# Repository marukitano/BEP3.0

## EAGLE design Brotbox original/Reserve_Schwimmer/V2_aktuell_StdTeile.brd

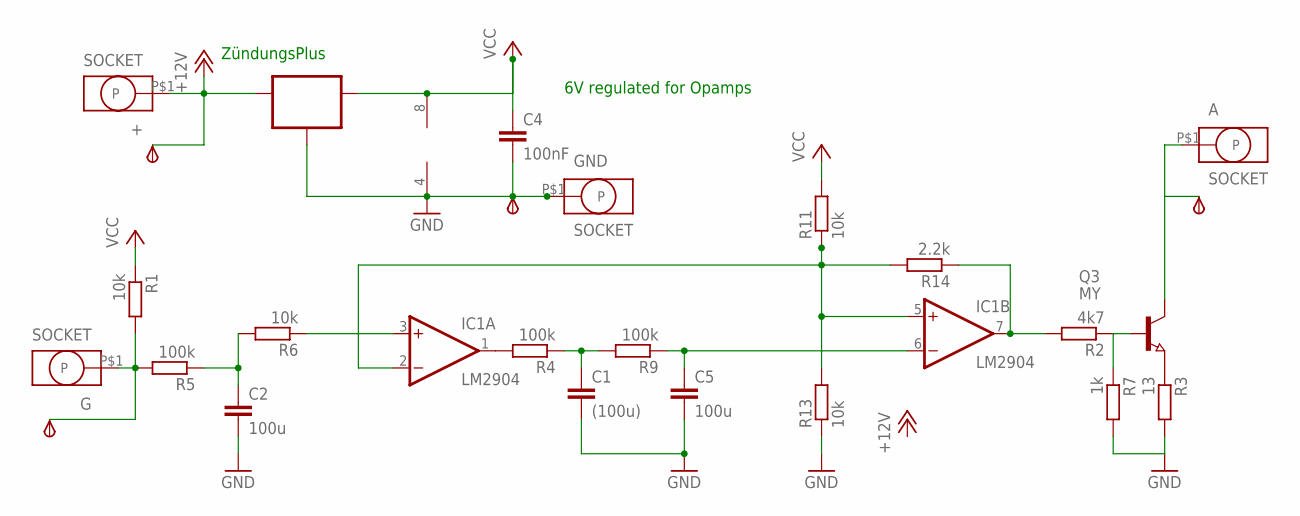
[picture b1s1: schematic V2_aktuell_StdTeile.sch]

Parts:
+: SOCKET; ID2.5MM
A: SOCKET; ID2.5MM
C1: (100u); C1206K
C2, C5: 100u; C1206K
C4: 100nF; C0805
G: SOCKET; ID2.5MM
GND: SOCKET; ID2.5MM
GND_: TPSB2.0; B2.0
IC1: LM2904; SO08
IC2: 70L06; SOT89_ROUND
IN: TPSB2.0; B2.0
OUT: TPSB2.0; B2.0
Q3: MY; SOT89
R1, R6, R11, R13: 10k; R0805
R2: 4k7; R0805
R3: 13; R1206
R4, R5, R9: 100k; R0805
R7: 1k; R0805
R14: 2.2k; R0805
V+: TPSB2.0; B2.0

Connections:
+12V: +.P$1, IC2.3 (IN), V+.TP
GND: C1.2, C2.2, C4.2, C5.2, GND.P$1, GND_.TP, IC1.4 (V-), IC2.2 (GND), IC2.2@1 (GND), R3.2, R7.2, R13.1
unnamed: C2.1, R5.1, R6.2
unnamed: Q3.1 (B), R2.1, R7.1
unnamed: C1.1, R4.1, R9.2
unnamed: C5.1, IC1.6 (-IN), R9.1
unnamed: IC1.2 (-IN), IC1.5 (+IN), R11.1, R13.2, R14.2
unnamed: G.P$1, IN.TP, R1.2, R5.2
unnamed: Q3.3 (E), R3.1
unnamed: IC1.3 (+IN), R6.1
unnamed: IC1.7 (OUT), R2.2, R14.1
unnamed: A.P$1, OUT.TP, Q3.2 (C)
unnamed: IC1.1 (OUT), R4.2
VCC: C4.1, IC1.8 (V+), IC2.1 (OUT), R1.1, R11.2

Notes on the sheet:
6V regulated for Opamps
ZündungsPlus

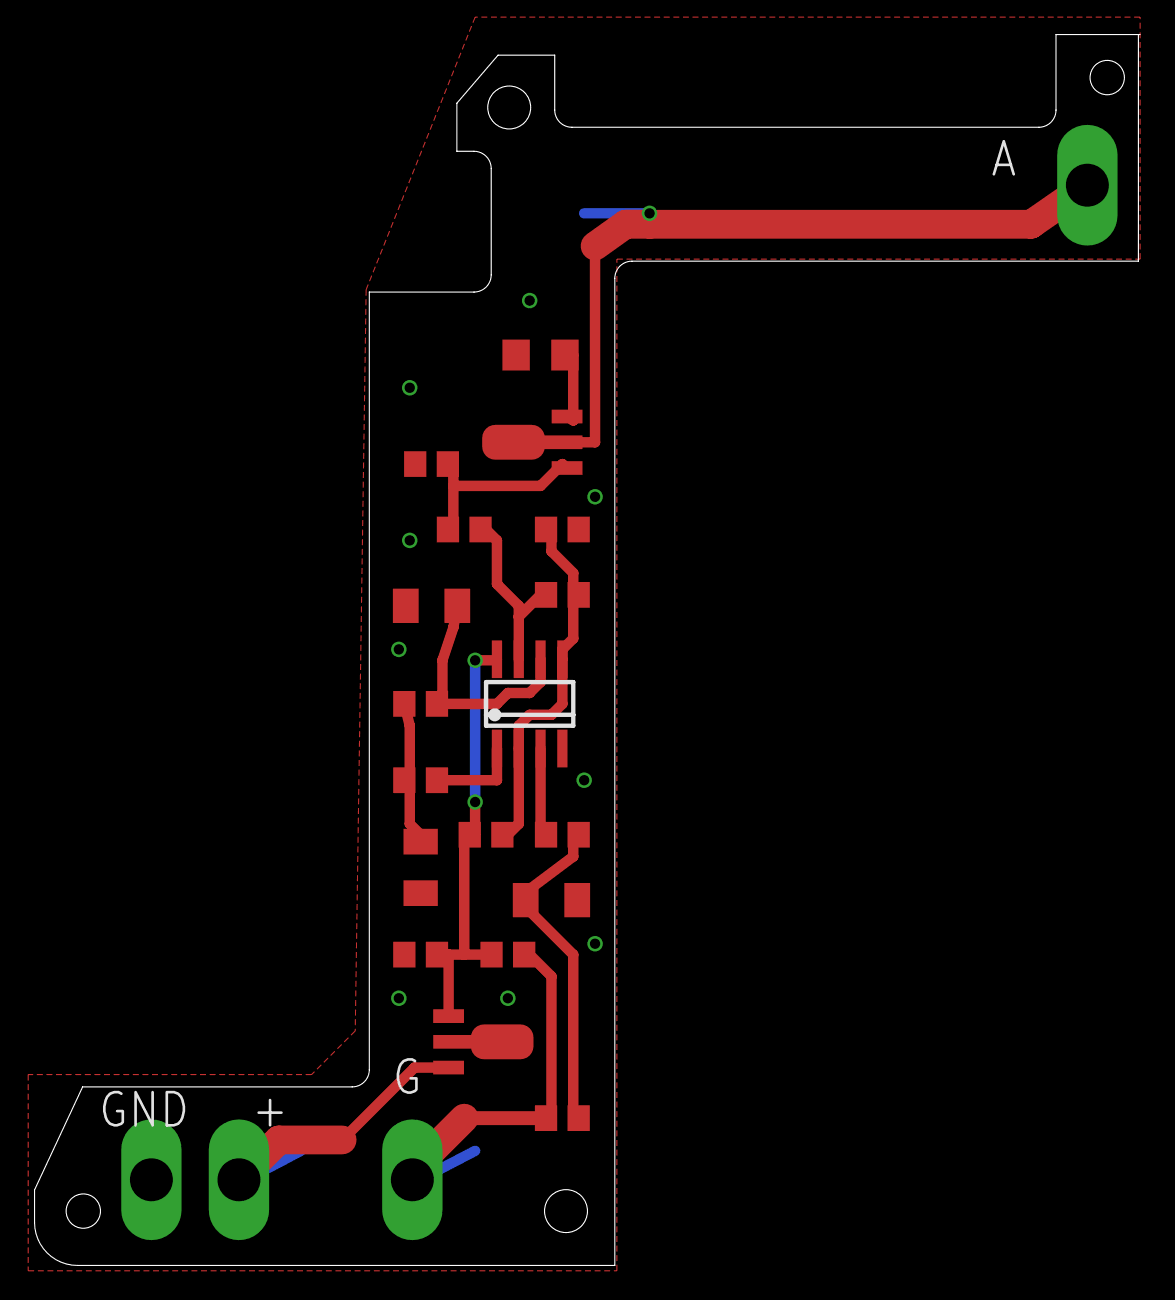
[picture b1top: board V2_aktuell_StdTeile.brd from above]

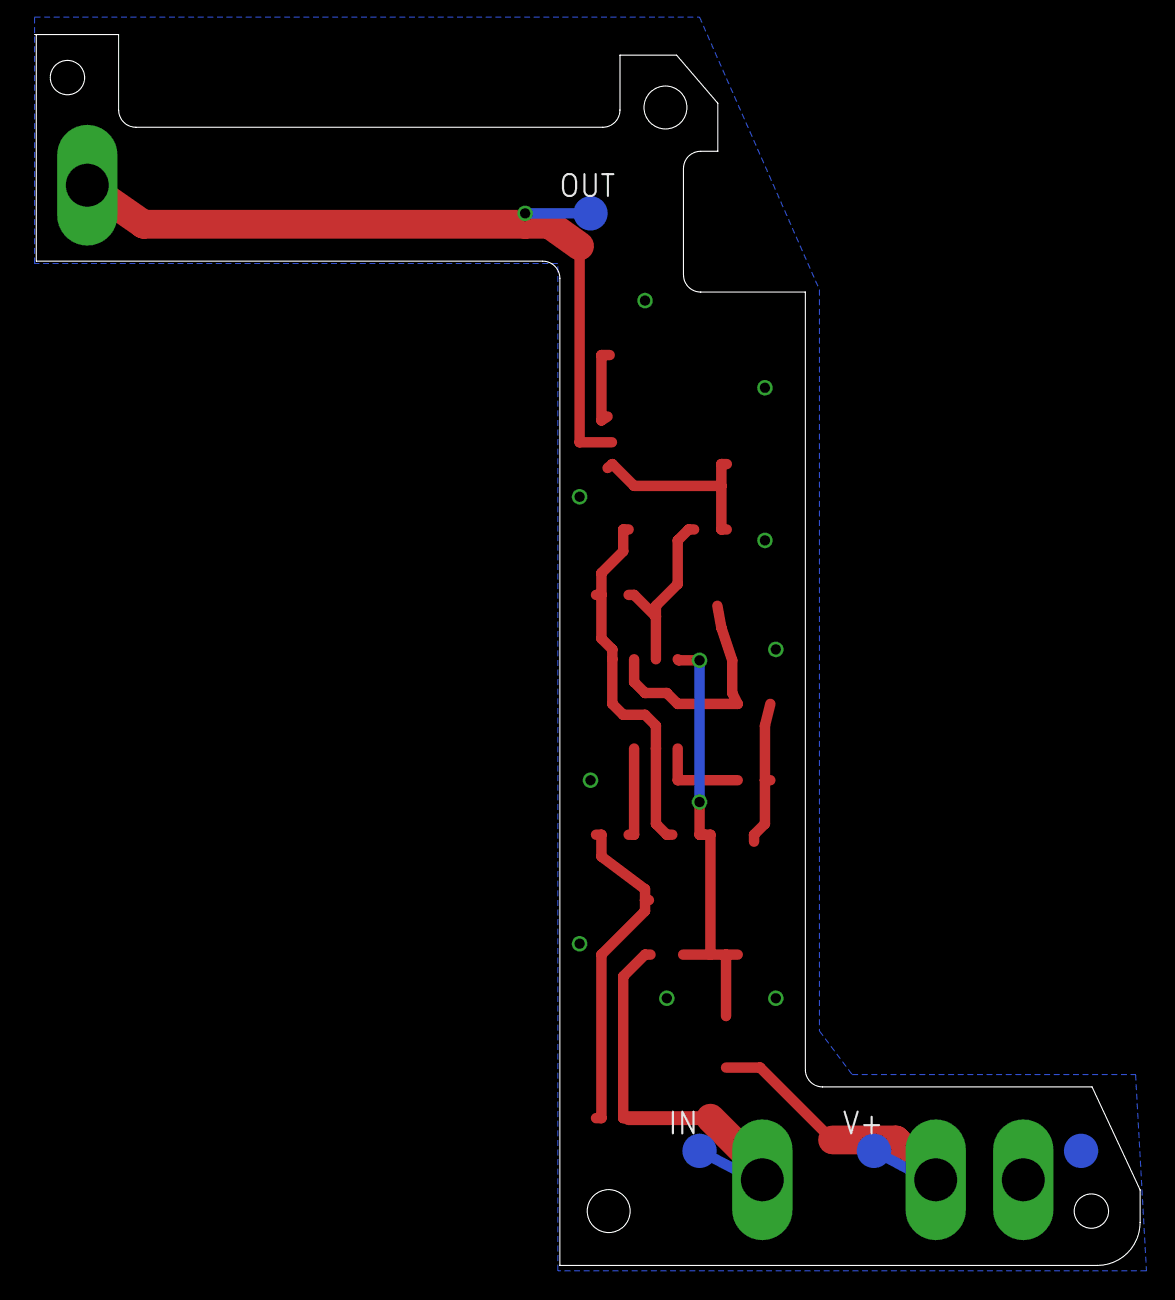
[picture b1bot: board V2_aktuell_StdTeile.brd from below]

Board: 2 copper layers, 64.3 x 71.7 mm, 26 parts (4 on the bottom side), 14 nets.

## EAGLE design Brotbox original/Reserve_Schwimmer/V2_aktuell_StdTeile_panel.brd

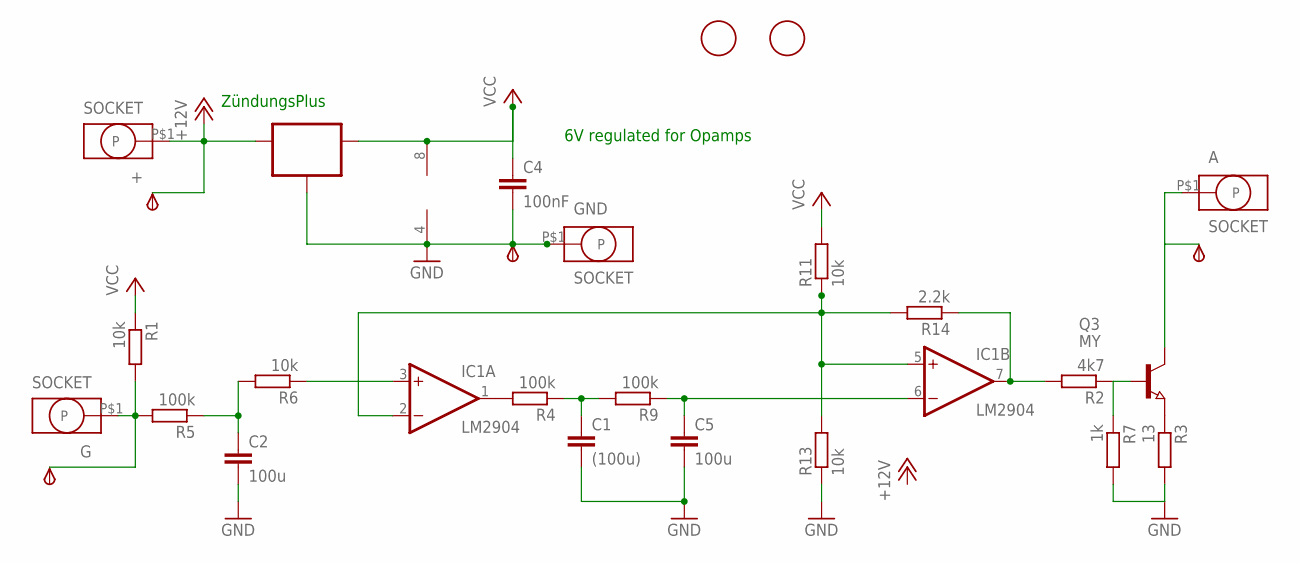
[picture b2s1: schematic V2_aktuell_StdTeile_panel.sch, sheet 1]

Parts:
+: SOCKET; ID2.5MM
A: SOCKET; ID2.5MM
C1: (100u); C1206K
C2, C5: 100u; C1206K
C4: 100nF; C0805
G: SOCKET; ID2.5MM
GND: SOCKET; ID2.5MM
GND_: TPSB2.0; B2.0
IC1: LM2904; SO08
IC2: 70L06; SOT89_ROUND
IN: TPSB2.0; B2.0
OUT: TPSB2.0; B2.0
Q3: MY; SOT89
R1, R6, R11, R13: 10k; R0805
R2: 4k7; R0805
R3: 13; R1206
R4, R5, R9: 100k; R0805
R7: 1k; R0805
R14: 2.2k; R0805
U$1, U$2: FIDUCIALFIDUCIAL_1MM_WITH_SOLDERMASK; FIDUCIAL_1MM_WITH_SOLDERMASK
V+: TPSB2.0; B2.0

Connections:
+12V: +.P$1, IC2.3 (IN), V+.TP; also elsewhere on the board
GND: C1.2, C2.2, C4.2, C5.2, GND.P$1, GND_.TP, IC1.4 (V-), IC2.2 (GND), IC2.2@1 (GND), R3.2, R7.2, R13.1; also elsewhere on the board
unnamed: C2.1, R5.1, R6.2
unnamed: Q3.1 (B), R2.1, R7.1
unnamed: C1.1, R4.1, R9.2
unnamed: C5.1, IC1.6 (-IN), R9.1
unnamed: IC1.2 (-IN), IC1.5 (+IN), R11.1, R13.2, R14.2
unnamed: G.P$1, IN.TP, R1.2, R5.2
unnamed: Q3.3 (E), R3.1
unnamed: IC1.3 (+IN), R6.1
unnamed: IC1.7 (OUT), R2.2, R14.1
unnamed: A.P$1, OUT.TP, Q3.2 (C)
unnamed: IC1.1 (OUT), R4.2
VCC: C4.1, IC1.8 (V+), IC2.1 (OUT), R1.1, R11.2; also elsewhere on the board

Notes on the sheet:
6V regulated for Opamps
ZündungsPlus

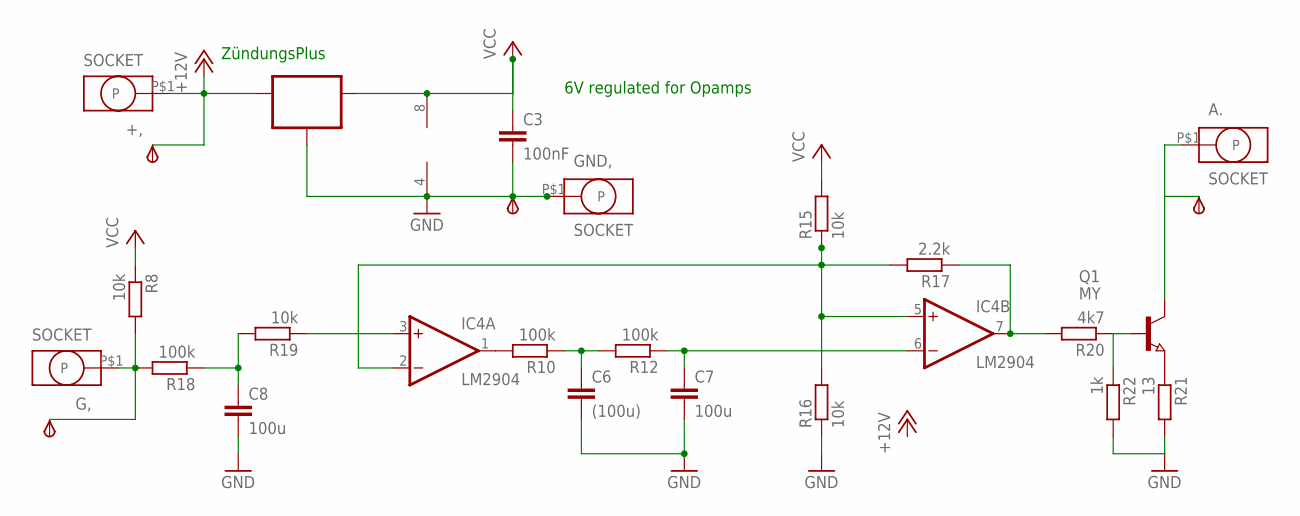
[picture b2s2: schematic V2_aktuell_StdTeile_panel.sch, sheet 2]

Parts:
+,: SOCKET; ID2.5MM
A.: SOCKET; ID2.5MM
C3: 100nF; C0805
C6: (100u); C1206K
C7, C8: 100u; C1206K
G,: SOCKET; ID2.5MM
GND,: SOCKET; ID2.5MM
GND_1: TPSB2.0; B2.0
IC3: 70L06; SOT89_ROUND
IC4: LM2904; SO08
IN,: TPSB2.0; B2.0
OUT.: TPSB2.0; B2.0
Q1: MY; SOT89
R8, R15, R16, R19: 10k; R0805
R10, R12, R18: 100k; R0805
R17: 2.2k; R0805
R20: 4k7; R0805
R21: 13; R1206
R22: 1k; R0805
V+,: TPSB2.0; B2.0

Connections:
+12V: +,.P$1, IC3.3 (IN), V+,.TP; also elsewhere on the board
GND: C3.2, C6.2, C7.2, C8.2, GND,.P$1, GND_1.TP, IC3.2 (GND), IC3.2@1 (GND), IC4.4 (V-), R16.1, R21.2, R22.2; also elsewhere on the board
unnamed: IC4.1 (OUT), R10.2
unnamed: C6.1, R10.1, R12.2
unnamed: C7.1, IC4.6 (-IN), R12.1
unnamed: IC4.2 (-IN), IC4.5 (+IN), R15.1, R16.2, R17.2
unnamed: IC4.7 (OUT), R17.1, R20.2
unnamed: C8.1, R18.1, R19.2
unnamed: G,.P$1, IN,.TP, R8.2, R18.2
unnamed: IC4.3 (+IN), R19.1
unnamed: Q1.1 (B), R20.1, R22.1
unnamed: A..P$1, OUT..TP, Q1.2 (C)
unnamed: Q1.3 (E), R21.1
VCC: C3.1, IC3.1 (OUT), IC4.8 (V+), R8.1, R15.2; also elsewhere on the board

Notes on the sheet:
6V regulated for Opamps
ZündungsPlus

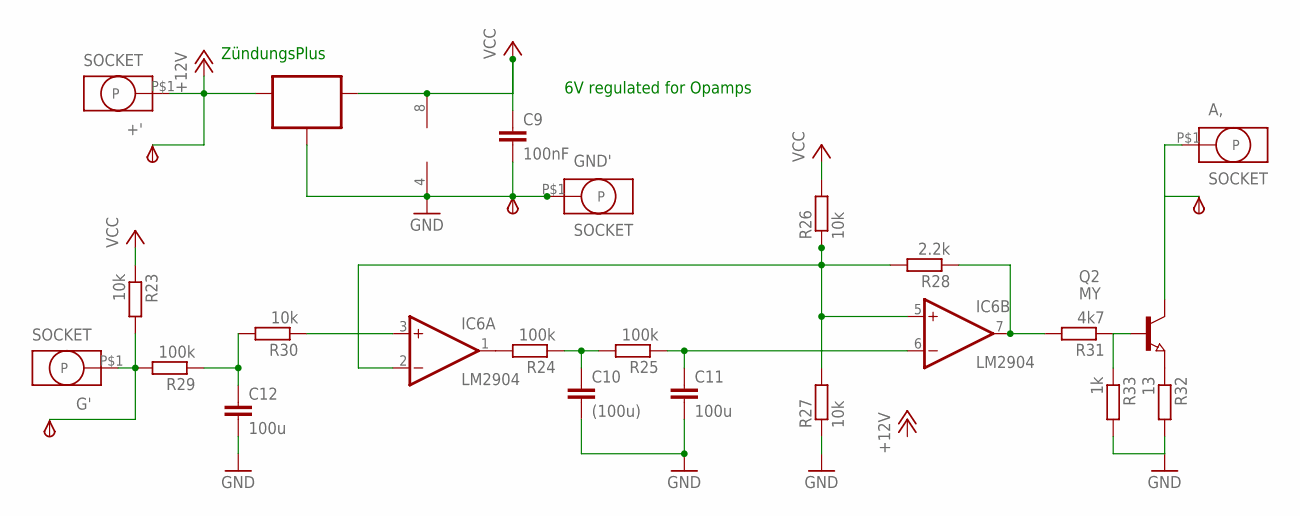
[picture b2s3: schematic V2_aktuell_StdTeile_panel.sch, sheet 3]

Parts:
+': SOCKET; ID2.5MM
A,: SOCKET; ID2.5MM
C9: 100nF; C0805
C10: (100u); C1206K
C11, C12: 100u; C1206K
G': SOCKET; ID2.5MM
GND': SOCKET; ID2.5MM
GND_2: TPSB2.0; B2.0
IC5: 70L06; SOT89_ROUND
IC6: LM2904; SO08
IN.: TPSB2.0; B2.0
OUT': TPSB2.0; B2.0
Q2: MY; SOT89
R23, R26, R27, R30: 10k; R0805
R24, R25, R29: 100k; R0805
R28: 2.2k; R0805
R31: 4k7; R0805
R32: 13; R1206
R33: 1k; R0805
V+.: TPSB2.0; B2.0

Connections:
+12V: +'.P$1, IC5.3 (IN), V+..TP; also elsewhere on the board
GND: C9.2, C10.2, C11.2, C12.2, GND'.P$1, GND_2.TP, IC5.2 (GND), IC5.2@1 (GND), IC6.4 (V-), R27.1, R32.2, R33.2; also elsewhere on the board
unnamed: IC6.1 (OUT), R24.2
unnamed: C10.1, R24.1, R25.2
unnamed: C11.1, IC6.6 (-IN), R25.1
unnamed: IC6.2 (-IN), IC6.5 (+IN), R26.1, R27.2, R28.2
unnamed: IC6.7 (OUT), R28.1, R31.2
unnamed: C12.1, R29.1, R30.2
unnamed: G'.P$1, IN..TP, R23.2, R29.2
unnamed: IC6.3 (+IN), R30.1
unnamed: Q2.1 (B), R31.1, R33.1
unnamed: A,.P$1, OUT'.TP, Q2.2 (C)
unnamed: Q2.3 (E), R32.1
VCC: C9.1, IC5.1 (OUT), IC6.8 (V+), R23.1, R26.2; also elsewhere on the board

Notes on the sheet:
6V regulated for Opamps
ZündungsPlus

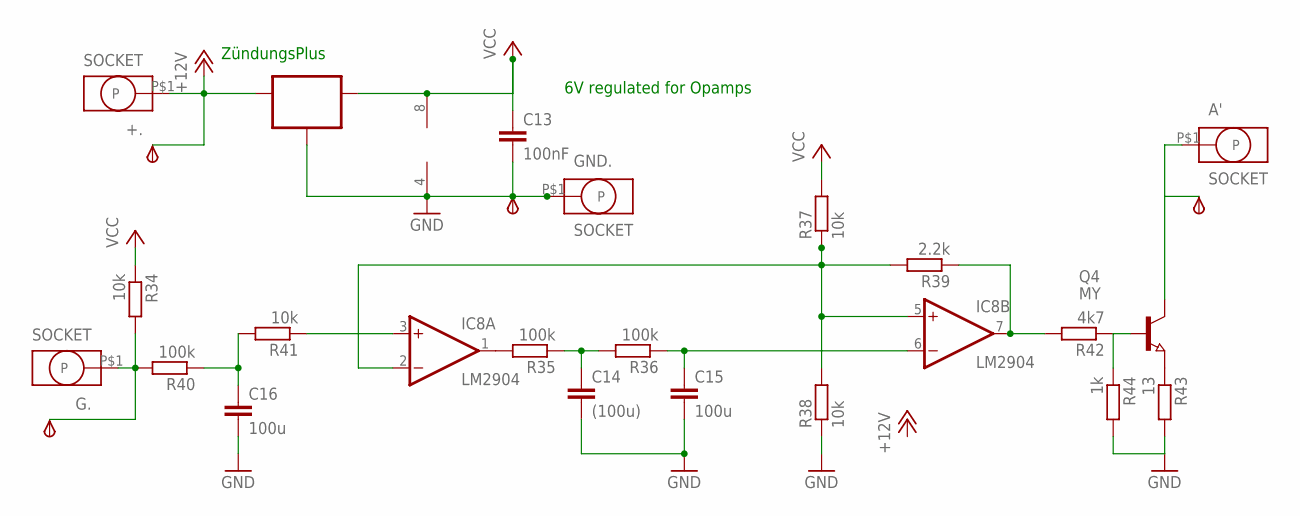
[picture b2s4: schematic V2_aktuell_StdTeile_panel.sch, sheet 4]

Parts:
+.: SOCKET; ID2.5MM
A': SOCKET; ID2.5MM
C13: 100nF; C0805
C14: (100u); C1206K
C15, C16: 100u; C1206K
G.: SOCKET; ID2.5MM
GND.: SOCKET; ID2.5MM
GND_3: TPSB2.0; B2.0
IC7: 70L06; SOT89_ROUND
IC8: LM2904; SO08
IN': TPSB2.0; B2.0
OUT,: TPSB2.0; B2.0
Q4: MY; SOT89
R34, R37, R38, R41: 10k; R0805
R35, R36, R40: 100k; R0805
R39: 2.2k; R0805
R42: 4k7; R0805
R43: 13; R1206
R44: 1k; R0805
V+': TPSB2.0; B2.0

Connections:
+12V: +..P$1, IC7.3 (IN), V+'.TP; also elsewhere on the board
GND: C13.2, C14.2, C15.2, C16.2, GND..P$1, GND_3.TP, IC7.2 (GND), IC7.2@1 (GND), IC8.4 (V-), R38.1, R43.2, R44.2; also elsewhere on the board
unnamed: IC8.1 (OUT), R35.2
unnamed: C14.1, R35.1, R36.2
unnamed: C15.1, IC8.6 (-IN), R36.1
unnamed: IC8.2 (-IN), IC8.5 (+IN), R37.1, R38.2, R39.2
unnamed: IC8.7 (OUT), R39.1, R42.2
unnamed: C16.1, R40.1, R41.2
unnamed: G..P$1, IN'.TP, R34.2, R40.2
unnamed: IC8.3 (+IN), R41.1
unnamed: Q4.1 (B), R42.1, R44.1
unnamed: A'.P$1, OUT,.TP, Q4.2 (C)
unnamed: Q4.3 (E), R43.1
VCC: C13.1, IC7.1 (OUT), IC8.8 (V+), R34.1, R37.2; also elsewhere on the board

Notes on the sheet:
6V regulated for Opamps
ZündungsPlus

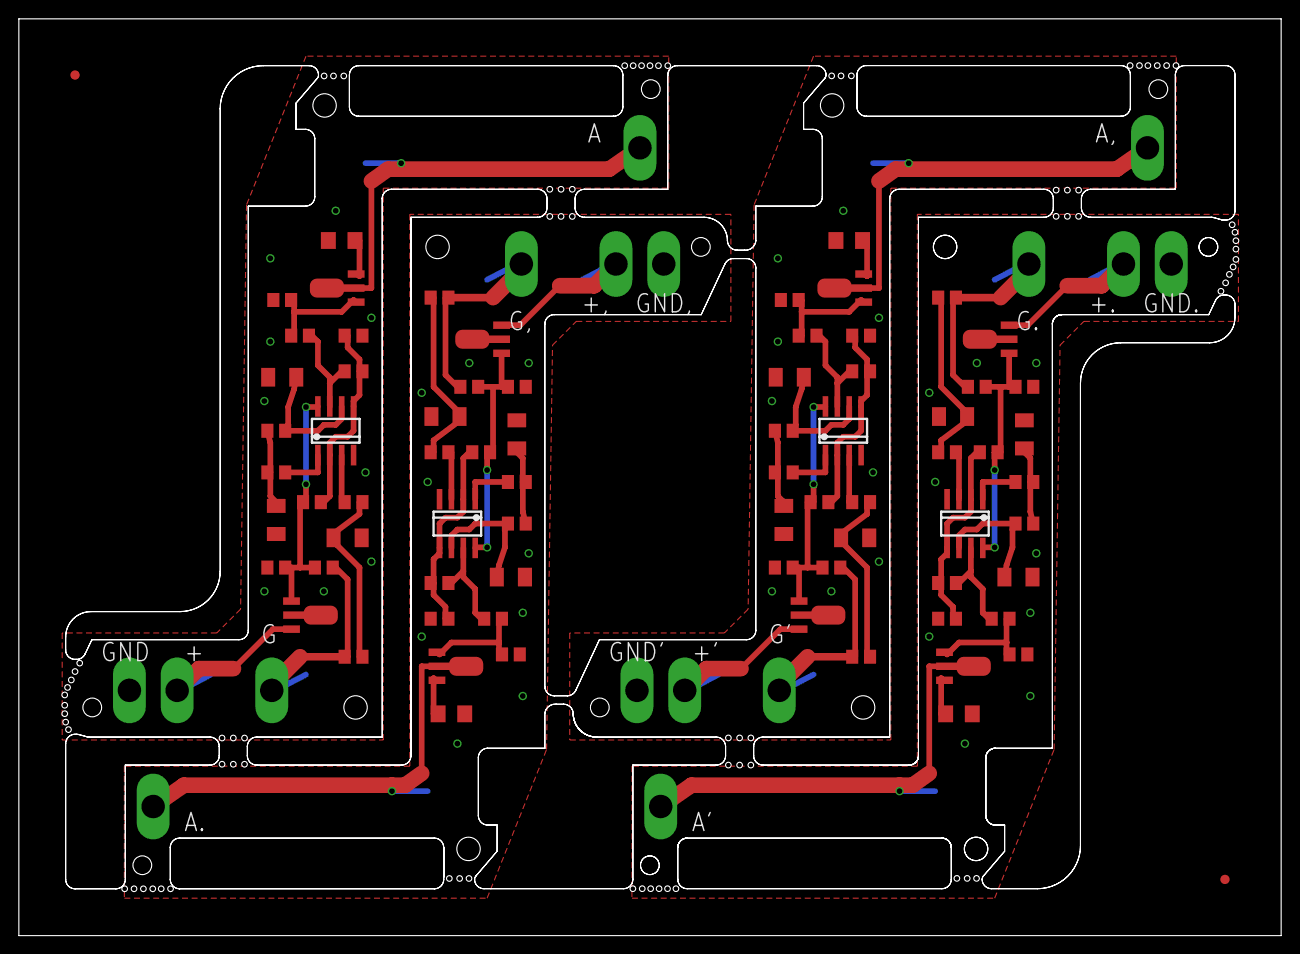
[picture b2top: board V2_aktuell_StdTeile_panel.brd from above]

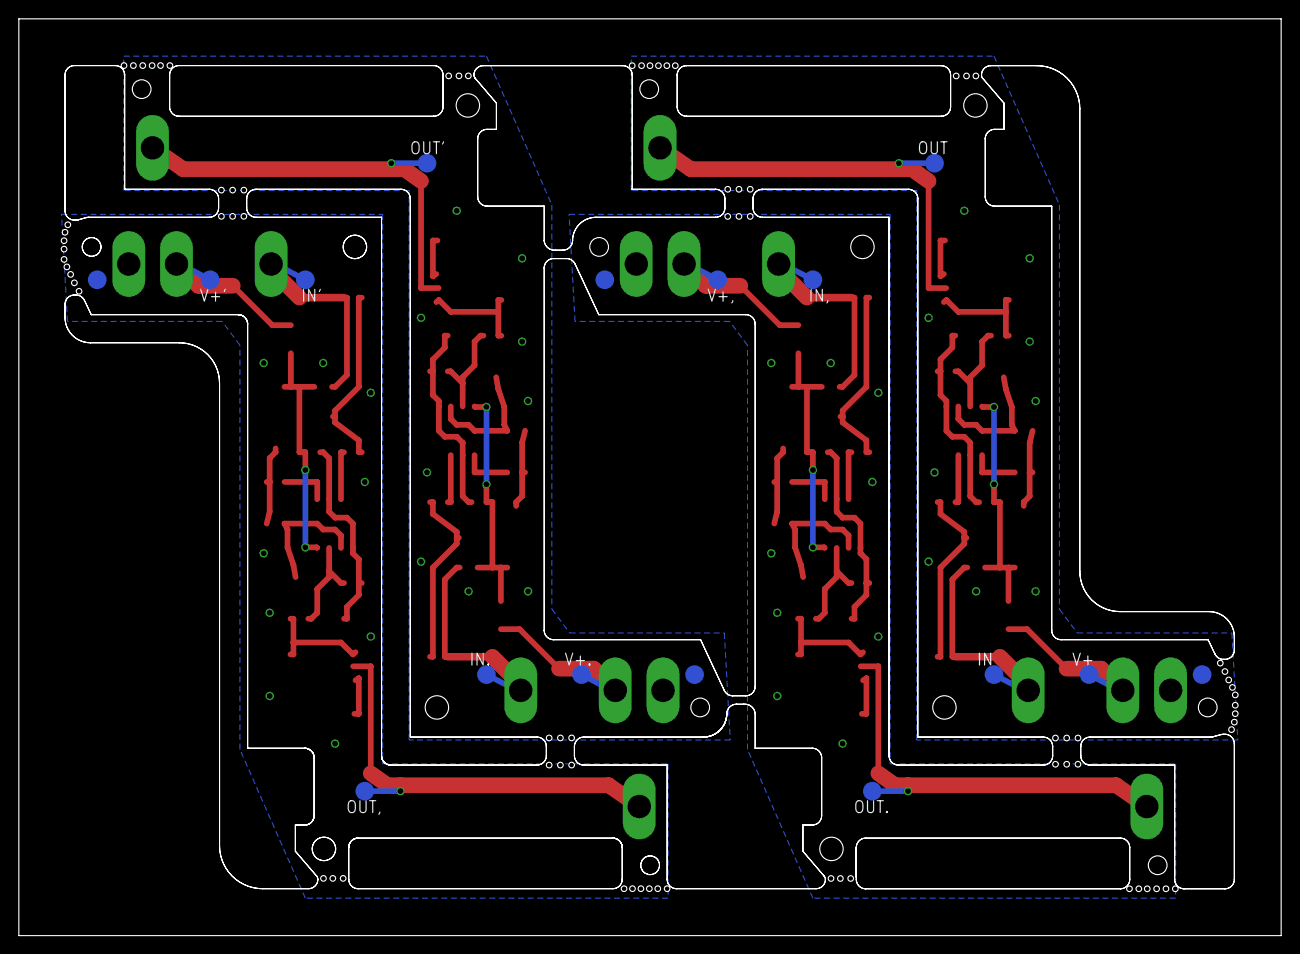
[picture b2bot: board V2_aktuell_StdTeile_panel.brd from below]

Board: 2 copper layers, 134.8 x 97.9 mm, 106 parts (16 on the bottom side), 47 nets.

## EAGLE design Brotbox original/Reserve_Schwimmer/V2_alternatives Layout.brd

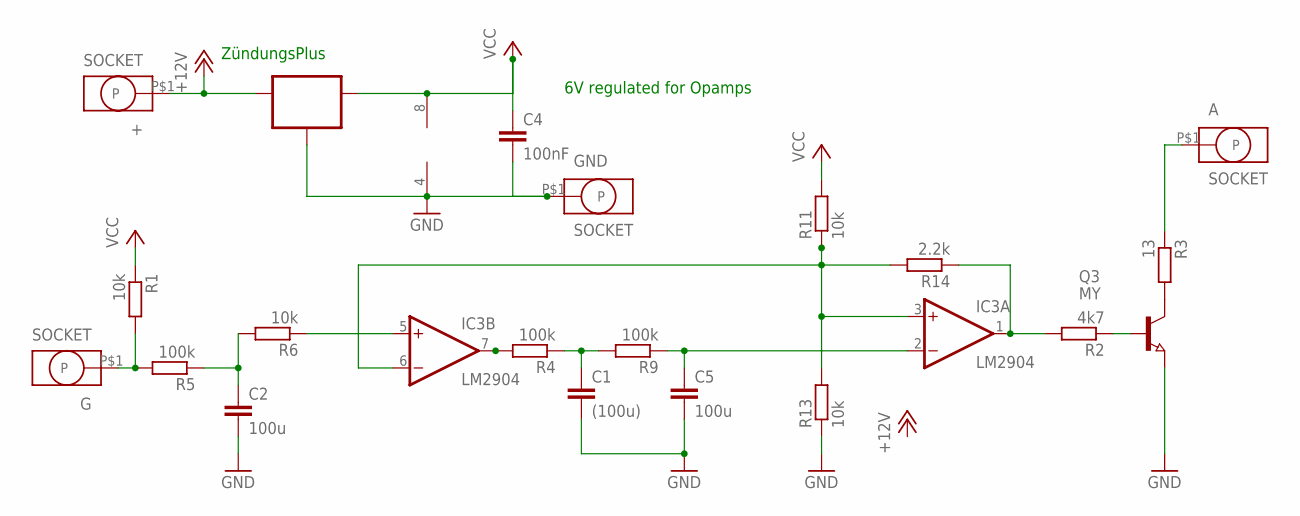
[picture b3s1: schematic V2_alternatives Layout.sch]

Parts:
+: SOCKET; ID2.5MM
A: SOCKET; ID2.5MM
C1: (100u); C1206K
C2, C5: 100u; C1206K
C4: 100nF; C0805
G: SOCKET; ID2.5MM
GND: SOCKET; ID2.5MM
IC2: 70L06; SOT89_ROUND
IC3: LM2904; SO08
Q3: MY; SOT89
R1, R6, R11, R13: 10k; R0805
R2: 4k7; R0805
R3: 13; R1206
R4, R5, R9: 100k; R0805
R14: 2.2k; R0805

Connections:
+12V: +.P$1, IC2.3 (IN)
GND: C1.2, C2.2, C4.2, C5.2, GND.P$1, IC2.2 (GND), IC2.2@1 (GND), IC3.4 (V-), Q3.3 (E), R13.1
unnamed: C2.1, R5.1, R6.2
unnamed: Q3.1 (B), R2.1
unnamed: C1.1, R4.1, R9.2
unnamed: C5.1, IC3.2 (-IN), R9.1
unnamed: IC3.3 (+IN), IC3.6 (-IN), R11.1, R13.2, R14.2
unnamed: G.P$1, R1.2, R5.2
unnamed: Q3.2 (C), R3.2
unnamed: IC3.5 (+IN), R6.1
unnamed: IC3.1 (OUT), R2.2, R14.1
unnamed: A.P$1, R3.1
unnamed: IC3.7 (OUT), R4.2
VCC: C4.1, IC2.1 (OUT), IC3.8 (V+), R1.1, R11.2

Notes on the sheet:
6V regulated for Opamps
ZündungsPlus

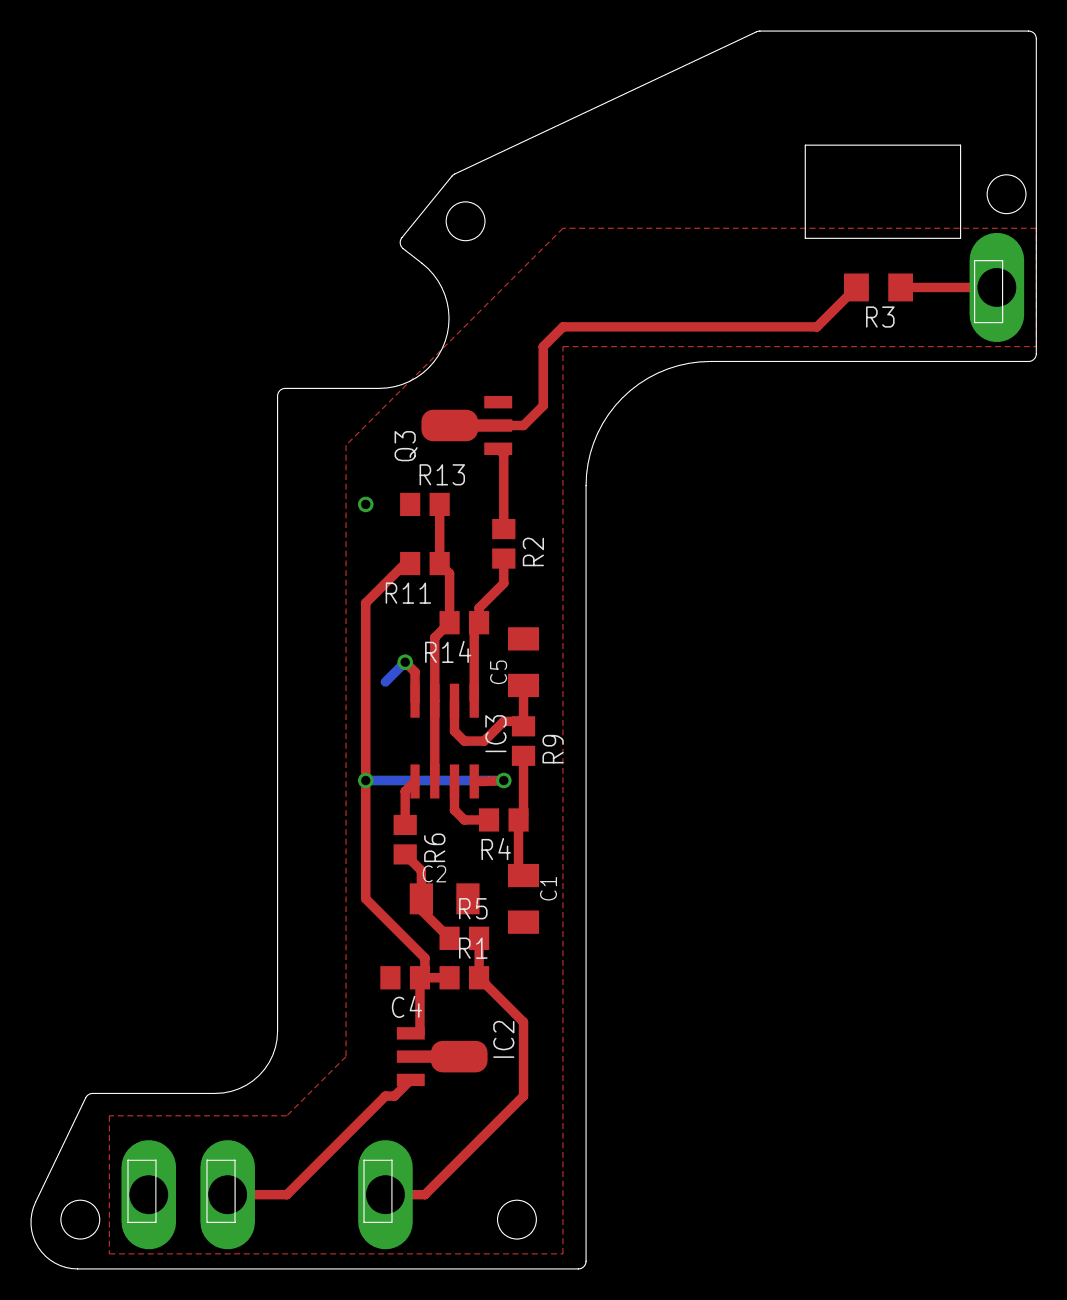
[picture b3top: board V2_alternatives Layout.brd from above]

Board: 2 copper layers, 64.7 x 79.7 mm, 21 parts (0 on the bottom side), 14 nets.

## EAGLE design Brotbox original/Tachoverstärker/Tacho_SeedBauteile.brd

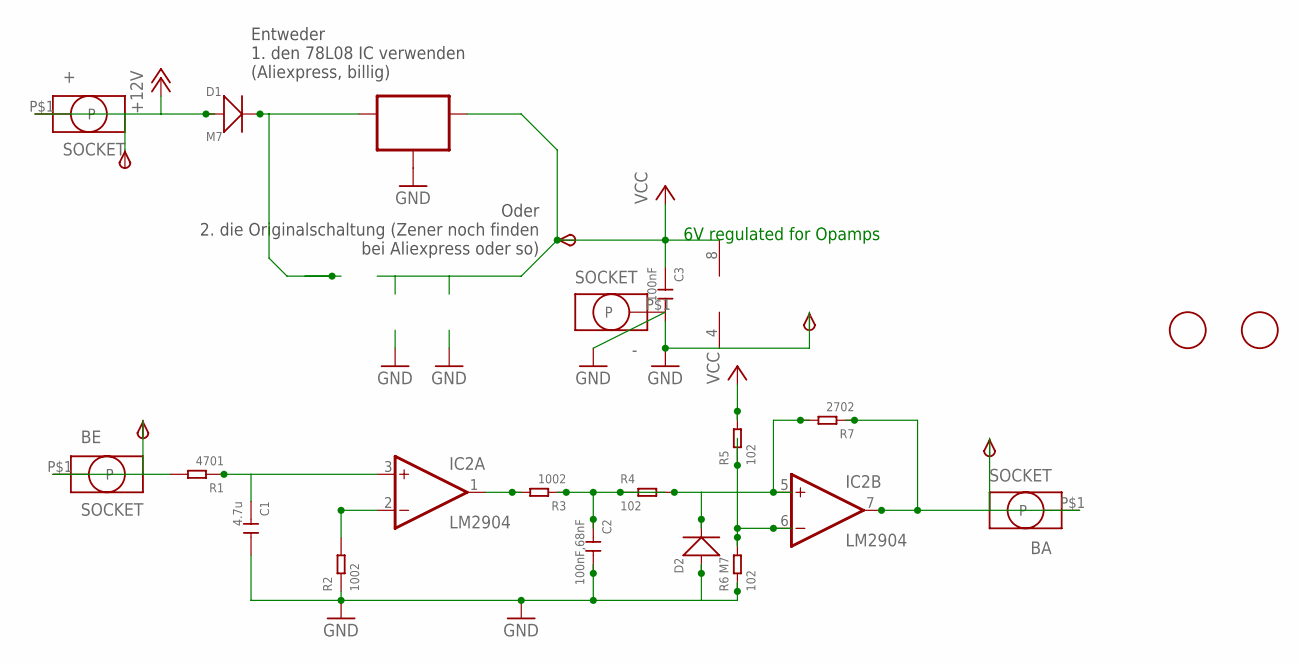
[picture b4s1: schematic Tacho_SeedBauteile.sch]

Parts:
6V: TPSB2.0; B2.0
+: SOCKET; ID2.5MM
+12V: TPSB2.0; B2.0
-: SOCKET; ID2.5MM
AUS: TPSB2.0; B2.0
BA: SOCKET; ID2.5MM
BE: SOCKET; ID2.5MM
C1: 4.7u; C0805
C2: 100nF,68nF; C0805
C3: 100nF; C0805
D1, D2: M7; DO-214AC
EIN: TPSB2.0; B2.0
FID1, FID2: FIDUCIAL; FIDUCIAL_1MM
GND: TPSB2.0; B2.0
IC1: 5V/6V oder 8V Regler; SOT89_ROUND
IC2: LM2904; SO08
R1: 4701; R0805
R2, R3: 1002; R0805
R4, R5, R6: 102; R0805
R7: 2702; R0805

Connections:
+12V: +.P$1, +12V.TP, D1.1 (+)
+12V1: AUS.TP, BA.P$1, IC2.7 (OUT), R7.1
GND: -.P$1, C1.2, C2.2, C3.2, D2.1 (+), GND.TP, IC1.2 (GND), IC1.2@1 (GND), IC2.4 (V-), R2.1, R6.1
unnamed: D1.2 (-), IC1.3 (IN)
unnamed: IC2.2 (-IN), R2.2
unnamed: BE.P$1, EIN.TP, R1.2
unnamed: C1.1, IC2.3 (+IN), R1.1
unnamed: IC2.1 (OUT), R3.2
unnamed: C2.1, R3.1, R4.1
unnamed: D2.2 (-), IC2.5 (+IN), R4.2, R7.2
unnamed: IC2.6 (-IN), R5.1, R6.2
VCC: 6V.TP, C3.1, IC1.1 (OUT), IC2.8 (V+), R5.2

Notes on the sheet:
6V regulated for Opamps
Entweder 1. den 78L08 IC verwenden (Aliexpress, billig)
Oder 2. die Originalschaltung (Zener noch finden bei Aliexpress oder so)

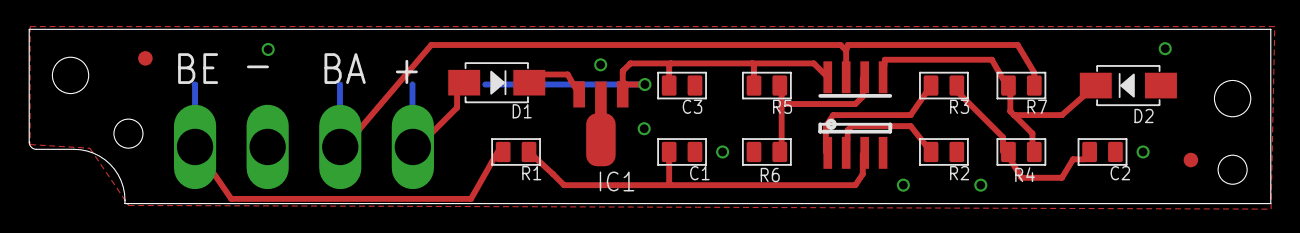
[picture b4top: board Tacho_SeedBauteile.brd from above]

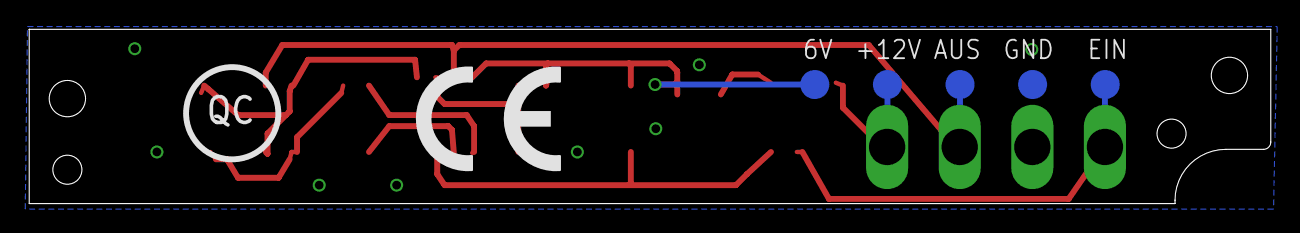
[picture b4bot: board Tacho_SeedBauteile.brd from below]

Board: 2 copper layers, 85.5 x 12.0 mm, 26 parts (6 on the bottom side), 12 nets.

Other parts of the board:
U$1: CE_10.00

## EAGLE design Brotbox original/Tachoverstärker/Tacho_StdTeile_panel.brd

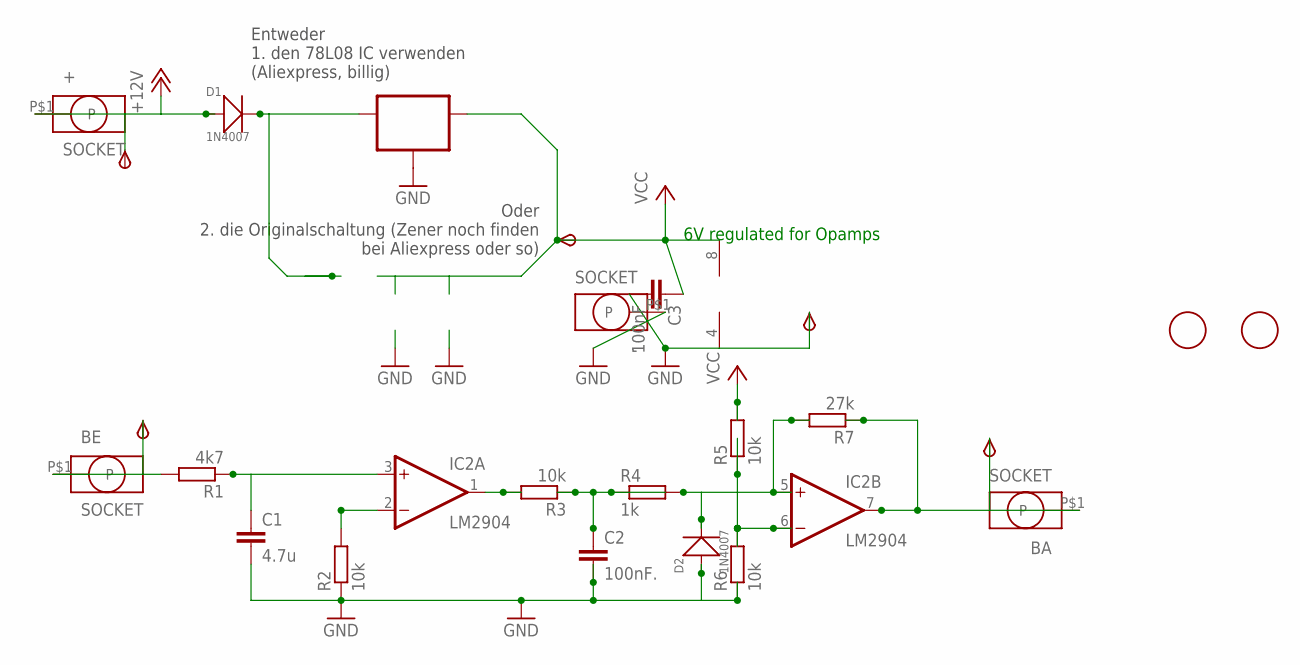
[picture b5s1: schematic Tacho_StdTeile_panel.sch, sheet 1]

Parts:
6V: TPSB2.0; B2.0
+: SOCKET; ID2.5MM
+12V: TPSB2.0; B2.0
-: SOCKET; ID2.5MM
AUS: TPSB2.0; B2.0
BA: SOCKET; ID2.5MM
BE: SOCKET; ID2.5MM
C1: 4.7u; C0805K
C2: 100nF.; C0805K
C3: 100nF; C0805K
D1, D2: 1N4007; DO-214AC
EIN: TPSB2.0; B2.0
FID2, FID20: FIDUCIAL; FIDUCIAL_1MM
GND: TPSB2.0; B2.0
IC1: 78L06; SOT89_ROUND
IC2: LM2904; SO08
R1: 4k7; R0805
R2, R3, R5, R6: 10k; R0805
R4: 1k; R0805
R7: 27k; R0805

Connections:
+12V: +.P$1, +12V.TP, D1.1 (+); also elsewhere on the board
+12V1: AUS.TP, BA.P$1, IC2.7 (OUT), R7.1
GND: -.P$1, C1.2, C2.2, C3.2, D2.1 (+), GND.TP, IC1.2 (GND), IC1.2@1 (GND), IC2.4 (V-), R2.1, R6.1; also elsewhere on the board
unnamed: D1.2 (-), IC1.3 (IN)
unnamed: IC2.2 (-IN), R2.2
unnamed: BE.P$1, EIN.TP, R1.2
unnamed: C1.1, IC2.3 (+IN), R1.1
unnamed: IC2.1 (OUT), R3.2
unnamed: C2.1, R3.1, R4.1
unnamed: D2.2 (-), IC2.5 (+IN), R4.2, R7.2
unnamed: IC2.6 (-IN), R5.1, R6.2
VCC: 6V.TP, C3.1, IC1.1 (OUT), IC2.8 (V+), R5.2; also elsewhere on the board

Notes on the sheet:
6V regulated for Opamps
Entweder 1. den 78L08 IC verwenden (Aliexpress, billig)
Oder 2. die Originalschaltung (Zener noch finden bei Aliexpress oder so)

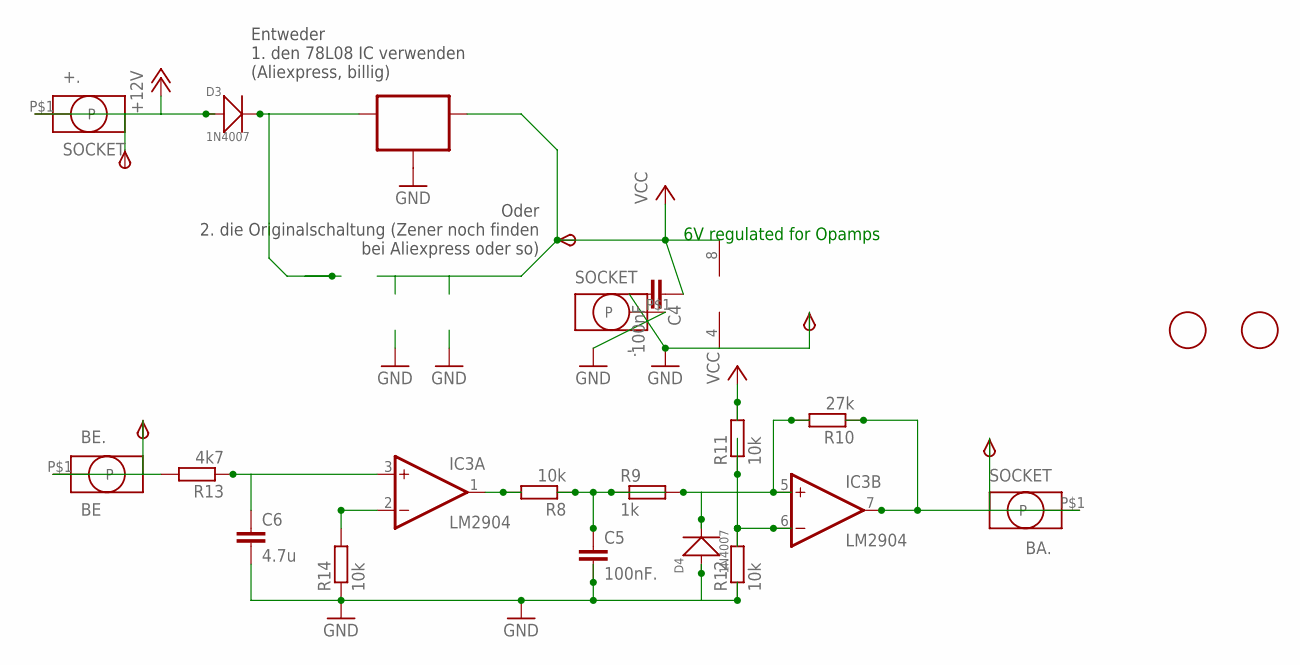
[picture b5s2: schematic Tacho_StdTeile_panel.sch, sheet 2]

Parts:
6V1: TPSB2.0; B2.0
+12V1: TPSB2.0; B2.0
+.: SOCKET; ID2.5MM
-.: SOCKET; ID2.5MM
AUS1: TPSB2.0; B2.0
BA.: SOCKET; ID2.5MM
BE.: BE; ID2.5MM
C4: 100nF; C0805K
C5: 100nF.; C0805K
C6: 4.7u; C0805K
D3, D4: 1N4007; DO-214AC
EIN1: TPSB2.0; B2.0
FID3, FID4: FIDUCIAL; FIDUCIAL_1MM
GND12: TPSB2.0; B2.0
IC3: LM2904; SO08
IC4: 78L06; SOT89_ROUND
R8, R11, R12, R14: 10k; R0805
R9: 1k; R0805
R10: 27k; R0805
R13: 4k7; R0805

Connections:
+12V: +12V1.TP, +..P$1, D3.1 (+); also elsewhere on the board
+12V2: AUS1.TP, BA..P$1, IC3.7 (OUT), R10.1
GND: -..P$1, C4.2, C5.2, C6.2, D4.1 (+), GND12.TP, IC3.4 (V-), IC4.2 (GND), IC4.2@1 (GND), R12.1, R14.1; also elsewhere on the board
unnamed: IC3.2 (-IN), R14.2
unnamed: IC3.1 (OUT), R8.2
unnamed: C5.1, R8.1, R9.1
unnamed: D4.2 (-), IC3.5 (+IN), R9.2, R10.2
unnamed: IC3.6 (-IN), R11.1, R12.2
unnamed: BE..P$1, EIN1.TP, R13.2
unnamed: C6.1, IC3.3 (+IN), R13.1
unnamed: D3.2 (-), IC4.3 (IN)
VCC: 6V1.TP, C4.1, IC3.8 (V+), IC4.1 (OUT), R11.2; also elsewhere on the board

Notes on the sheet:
6V regulated for Opamps
Entweder 1. den 78L08 IC verwenden (Aliexpress, billig)
Oder 2. die Originalschaltung (Zener noch finden bei Aliexpress oder so)

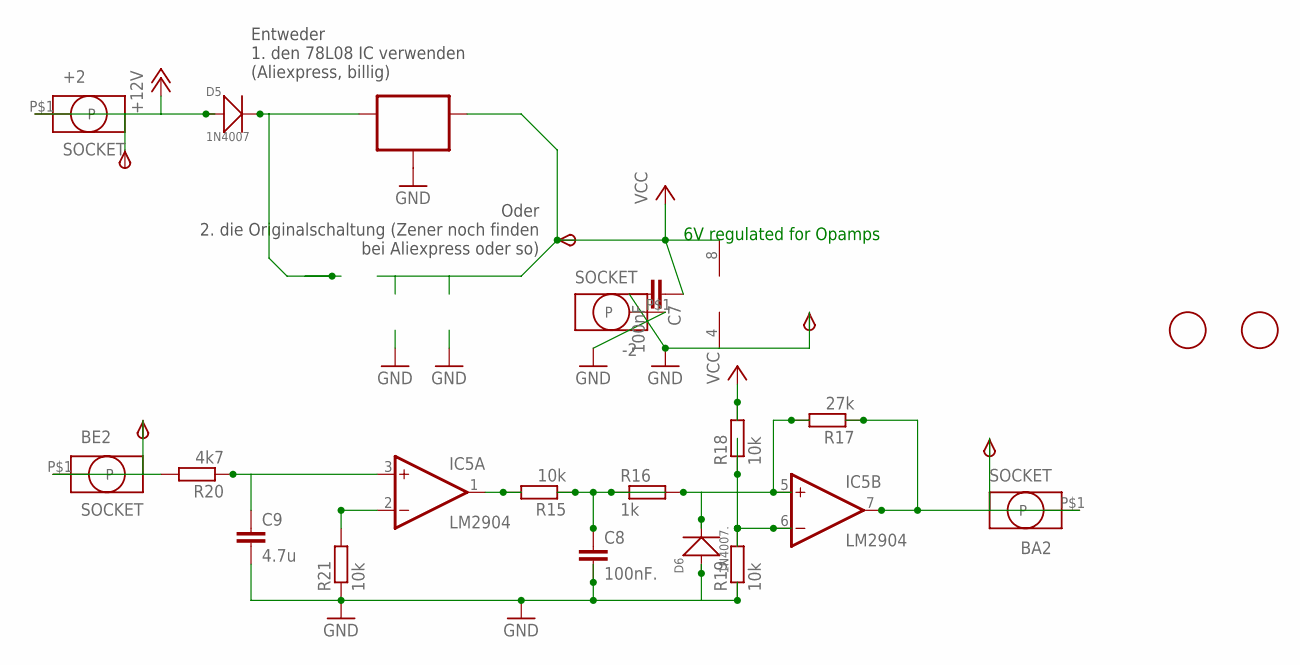
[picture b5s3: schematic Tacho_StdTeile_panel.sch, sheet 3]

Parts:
6V2: TPSB2.0; B2.0
+2: SOCKET; ID2.5MM
+12V2: TPSB2.0; B2.0
-2: SOCKET; ID2.5MM
AUS2: TPSB2.0; B2.0
BA2: SOCKET; ID2.5MM
BE2: SOCKET; ID2.5MM
C7: 100nF; C0805K
C8: 100nF.; C0805K
C9: 4.7u; C0805K
D5: 1N4007; DO-214AC
D6: 1N4007.; DO-214AC
EIN2: TPSB2.0; B2.0
FID5, FID6: FIDUCIAL; FIDUCIAL_1MM
GND20: TPSB2.0; B2.0
IC5: LM2904; SO08
IC6: 78L06; SOT89_ROUND
R15, R18, R19, R21: 10k; R0805
R16: 1k; R0805
R17: 27k; R0805
R20: 4k7; R0805

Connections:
+12V: +2.P$1, +12V2.TP, D5.1 (+); also elsewhere on the board
+12V3: AUS2.TP, BA2.P$1, IC5.7 (OUT), R17.1
GND: -2.P$1, C7.2, C8.2, C9.2, D6.1 (+), GND20.TP, IC5.4 (V-), IC6.2 (GND), IC6.2@1 (GND), R19.1, R21.1; also elsewhere on the board
unnamed: IC5.2 (-IN), R21.2
unnamed: IC5.1 (OUT), R15.2
unnamed: C8.1, R15.1, R16.1
unnamed: D6.2 (-), IC5.5 (+IN), R16.2, R17.2
unnamed: IC5.6 (-IN), R18.1, R19.2
unnamed: BE2.P$1, EIN2.TP, R20.2
unnamed: C9.1, IC5.3 (+IN), R20.1
unnamed: D5.2 (-), IC6.3 (IN)
VCC: 6V2.TP, C7.1, IC5.8 (V+), IC6.1 (OUT), R18.2; also elsewhere on the board

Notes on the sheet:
6V regulated for Opamps
Entweder 1. den 78L08 IC verwenden (Aliexpress, billig)
Oder 2. die Originalschaltung (Zener noch finden bei Aliexpress oder so)
